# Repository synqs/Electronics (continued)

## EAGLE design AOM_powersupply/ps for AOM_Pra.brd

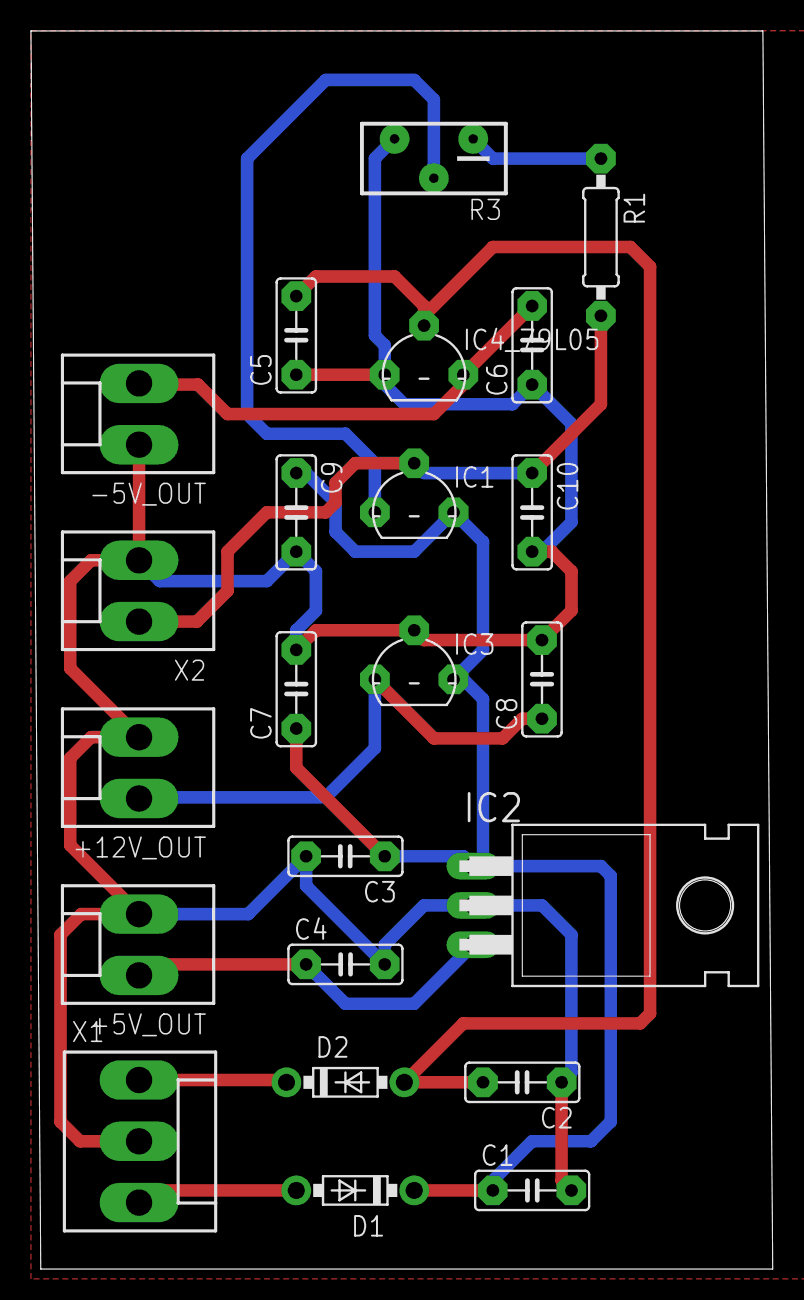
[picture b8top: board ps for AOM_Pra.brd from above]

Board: 2 copper layers, 47.9 x 80.0 mm, 23 parts (0 on the bottom side), 11 nets.

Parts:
+5V_OUT, +12V_OUT: KK-156-2
-5V_OUT: KK-156-2
C1, C2: 47uF; C050-025X075
C3, C5, C7, C9: 1uF; C050-025X075
C4, C6, C8, C10: 10uF; C050-025X075
D1, D2: 1N5817-B; DO41-7.6
IC1: LM317LZ; TO92
IC2: 7805T; TO220H
IC3: 78L12Z; TO92
IC4_79L05: TO92
R1: 150; 0207/10
R3: RTRIM3296Y
X1: KK-156-3
X2: KK-156-2

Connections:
+24V: C1.1, C3.1, C7.1, C9.1, D1.C, IC1.3, IC2.1, IC3.3
-24V: C2.2, C5.2, D2.A, IC4_79L05.2
GND: +5V_OUT.2, +12V_OUT.2, -5V_OUT.1, C1.2, C2.1, C3.2, C4.2, C5.1, C6.1, C7.2, C8.2, C9.2, C10.2, IC2.2, IC3.2, IC4_79L05.1, R3.3, X1.2, X2.2
unnamed: D2.C, X1.1
unnamed: D1.A, X1.3
unnamed: +12V_OUT.1, C8.1, IC3.1
unnamed: +5V_OUT.1, C4.1, IC2.3
unnamed: -5V_OUT.2, C6.2, IC4_79L05.3
unnamed: R1.1, R3.1
unnamed: IC1.1, R3.2
unnamed: C10.1, IC1.2, R1.2, X2.1

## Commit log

2016-05-04 add README
2016-05-04 added the already present electronics files.
2016-05-10 first version of the simple PD board.
2016-05-10 updated the simple design to be conform with our milling machine. Started a project with an integrated battery
2016-06-03 A very simple Transimpedence design. The version we finally test is the version AZ_SMD
2016-06-27 updated the PD board. PD is now properly connected and removed the BNC connectors.
2016-06-27 updated the PD board. PD was always properly connected. Now the symbol corresponds also to the PD we have.
2016-06-27 and add a picture of the new design.
2016-07-04 replaced the OP27 by a TL071 in the TI circuit
2016-07-14 changed the board to be photovoltaic and removed one useless Capa
2016-07-15 created the project for the magnetic field sensor.
2016-07-15 moved the projects out of the Eagle folder
2016-07-19 Added a guide for milling
    Added the user guide for the magnetic field sensor.
2016-07-20 - Updated the sensor amplification to follow the eurocircuits rules. - Replaced op-amp of small pitch to have a larger pitch - Ordered the text on the board a bit more
2016-07-20 made the board compatible with the PCB rules.
2017-01-03 added the shutter board and the AOM power supply by Pra
2017-02-07 Add two new versions of the power supply board. The version with _AZ has a minimized footprint. The version _Pra is larger, but might be easier to soder.
2017-02-14 Updated the simplePD board. — It is not in photovoltaic mode. — The capacitors are better located. — We added a serial resistor for 50Ohm termination. — The power connectors are closer by.
2017-02-14 New PID board
    Added this PID board, which was developed by Helmut Strobel and Tilman
    Zibold for simple usage.
